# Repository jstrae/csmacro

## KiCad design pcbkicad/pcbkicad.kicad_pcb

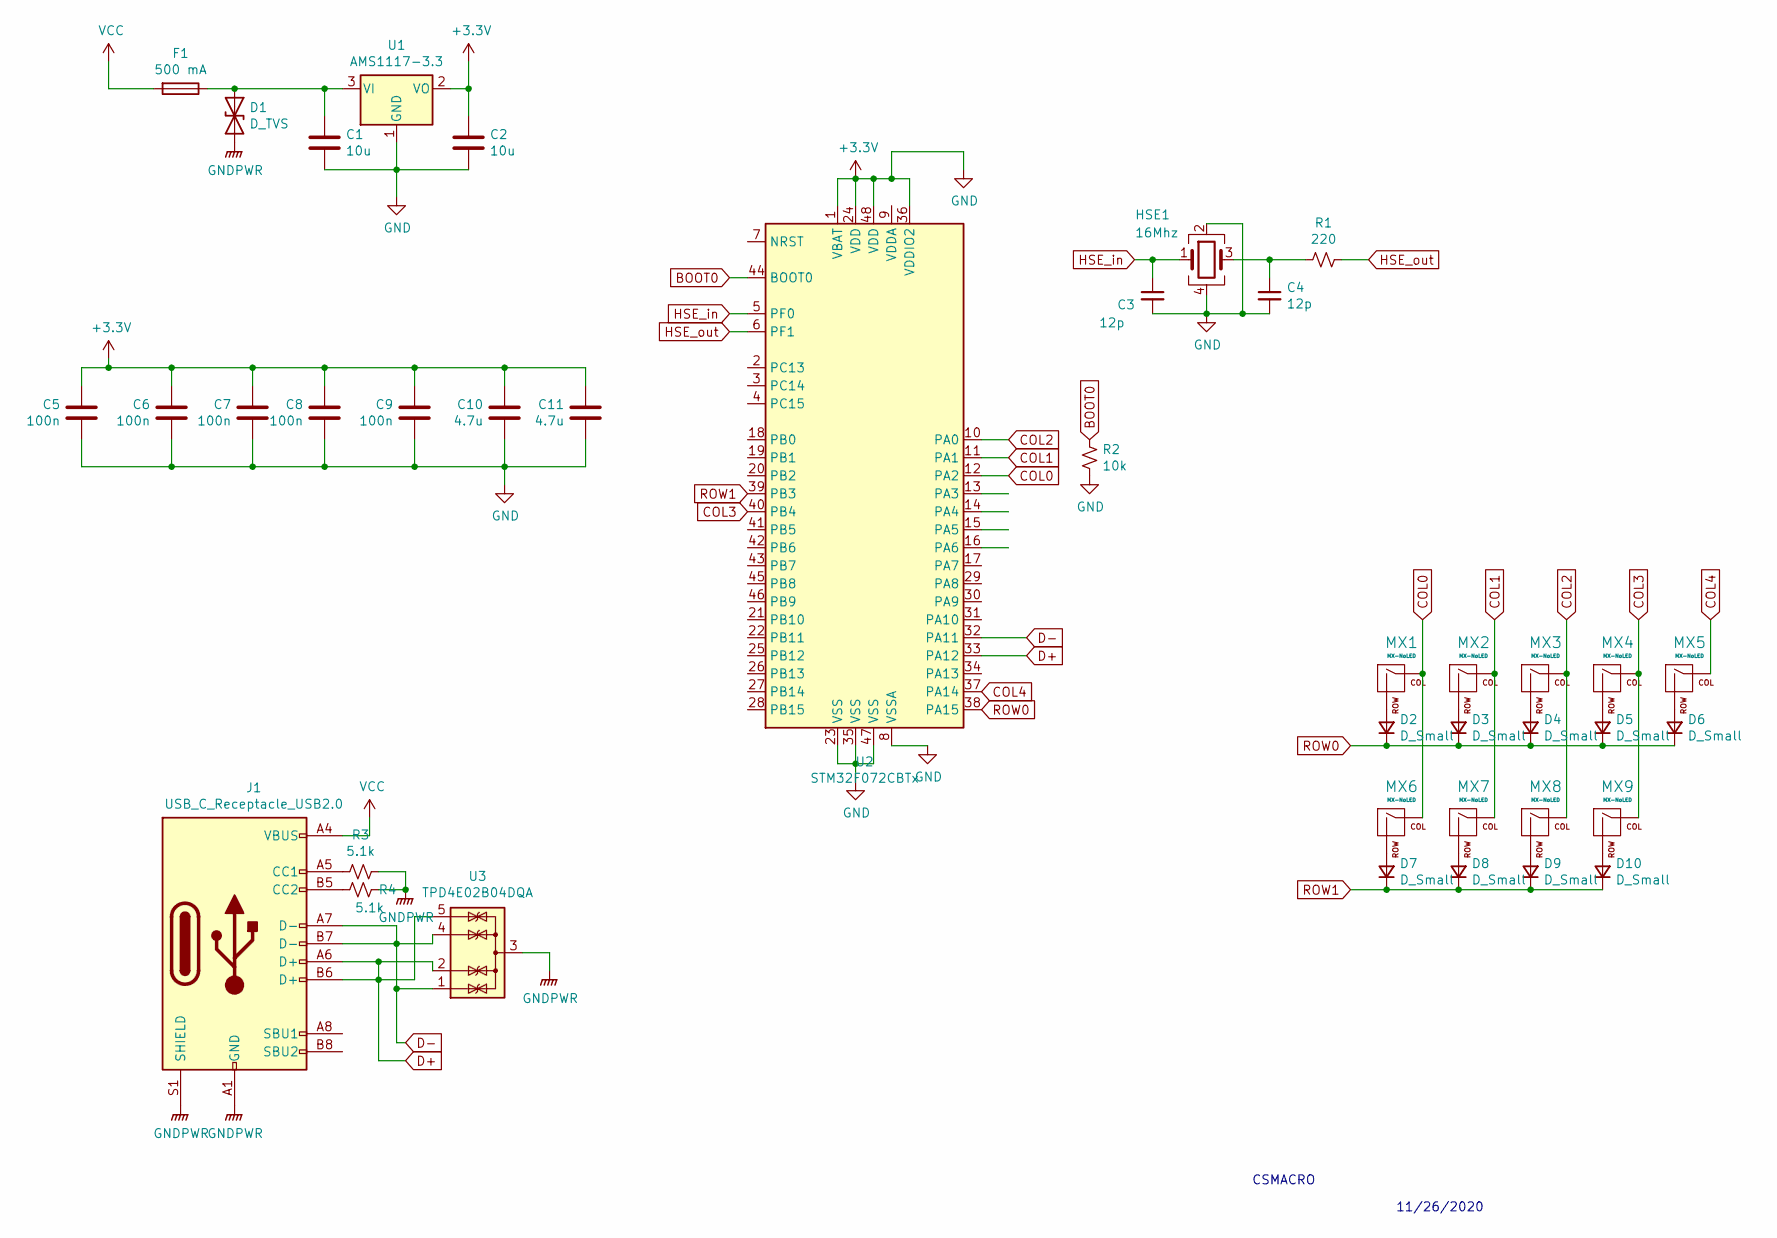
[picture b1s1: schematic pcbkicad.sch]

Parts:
C1: 10u; JST_SH_SM04B-SRSS-TB_1x04-1MP_P1.00mm_Horizontal
C2: 10u; C_0805_2012Metric
C3, C4: 12p; C_0805_2012Metric
C5, C6, C7, C8, C9: 100n; C_0805_2012Metric
C10, C11: 4.7u; C_0805_2012Metric
D1: D_TVS; D_0201_0603Metric
D2, D3, D4, D5, D6, D7, D8, D9, D10: D_Small; D_SOD-123
F1: 500 mA; Fuse_0402_1005Metric
HSE1: 16Mhz; Crystal_SMD_3225-4Pin_3.2x2.5mm
J1: USB_C_Receptacle_USB2.0; USB_C_Receptacle_HRO_TYPE-C-31-M-12
MX1, MX2, MX3, MX4, MX5, MX6, MX7, MX8, MX9: MX-NoLED; SW_Cherry_MX_1.00u_PCB
R1: 220; R_0805_2012Metric
R2: 10k; R_0805_2012Metric
R3, R4: 5.1k; R_0805_2012Metric
U1: AMS1117-3.3; SOT-223-3_TabPin2
U2: STM32F072CBTx; LQFP-48_7x7mm_P0.5mm
U3: TPD4E02B04DQA; USON-10_2.5x1.0mm_P0.5mm

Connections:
+3V3: C1.2, C2.1, C2.2, C3.2, C4.2, C5.1, C5.2, C6.1, C6.2, C7.1, C7.2, C8.1, C8.2, C9.1, C9.2, C10.1, C10.2, C11.1, C11.2, HSE1.2, HSE1.4, R2.2, U1.1 (GND), U1.2 (VO), U2.1 (VBAT), U2.8 (VSSA), U2.23 (VSS), U2.24 (VDD), U2.35 (VSS), U2.36 (VDDIO2), U2.47 (VSS), U2.48 (VDD)
BOOT0: R2.1, U2.44 (BOOT0)
COL0: MX1.1 (COL), MX6.1 (COL), U2.12 (PA2)
COL1: MX2.1 (COL), MX7.1 (COL), U2.11 (PA1)
COL2: MX3.1 (COL), MX8.1 (COL), U2.10 (PA0)
COL3: MX4.1 (COL), MX9.1 (COL), U2.40 (PB4)
COL4: MX5.1 (COL), U2.37 (PA14)
D+: J1.A6 (D+), J1.B6 (D+), U2.33 (PA12), U3.2 (IO2), U3.5 (IO4)
D-: J1.A7 (D-), J1.B7 (D-), U2.32 (PA11), U3.1 (IO1), U3.4 (IO3)
GNDPWR: D1.2 (A2), J1.A1 (GND), J1.A12 (GND), J1.B1 (GND), J1.B12 (GND), J1.S1 (SHIELD), R3.1, R4.1, U3.3 (G), U3.8 (G)
HSE_in: C3.1, HSE1.1, U2.5 (PF0)
HSE_out: R1.1, U2.6 (PF1)
unnamed: C1.1, D1.1 (A1), F1.1, U1.3 (VI)
unnamed: C4.1, HSE1.3, R1.2
unnamed: D2.2 (A), MX1.2 (ROW)
unnamed: D3.2 (A), MX2.2 (ROW)
unnamed: D4.2 (A), MX3.2 (ROW)
unnamed: D5.2 (A), MX4.2 (ROW)
unnamed: D6.2 (A), MX5.2 (ROW)
unnamed: D7.2 (A), MX6.2 (ROW)
unnamed: D8.2 (A), MX7.2 (ROW)
unnamed: D9.2 (A), MX8.2 (ROW)
unnamed: D10.2 (A), MX9.2 (ROW)
unnamed: J1.A5 (CC1), R3.2
unnamed: J1.B5 (CC2), R4.2
ROW0: D2.1 (K), D3.1 (K), D4.1 (K), D5.1 (K), D6.1 (K), U2.38 (PA15)
ROW1: D7.1 (K), D8.1 (K), D9.1 (K), D10.1 (K), U2.39 (PB3)
VCC: F1.2, J1.A4 (VBUS), J1.A9 (VBUS), J1.B4 (VBUS), J1.B9 (VBUS)

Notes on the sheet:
CSMACRO
11/26/2020

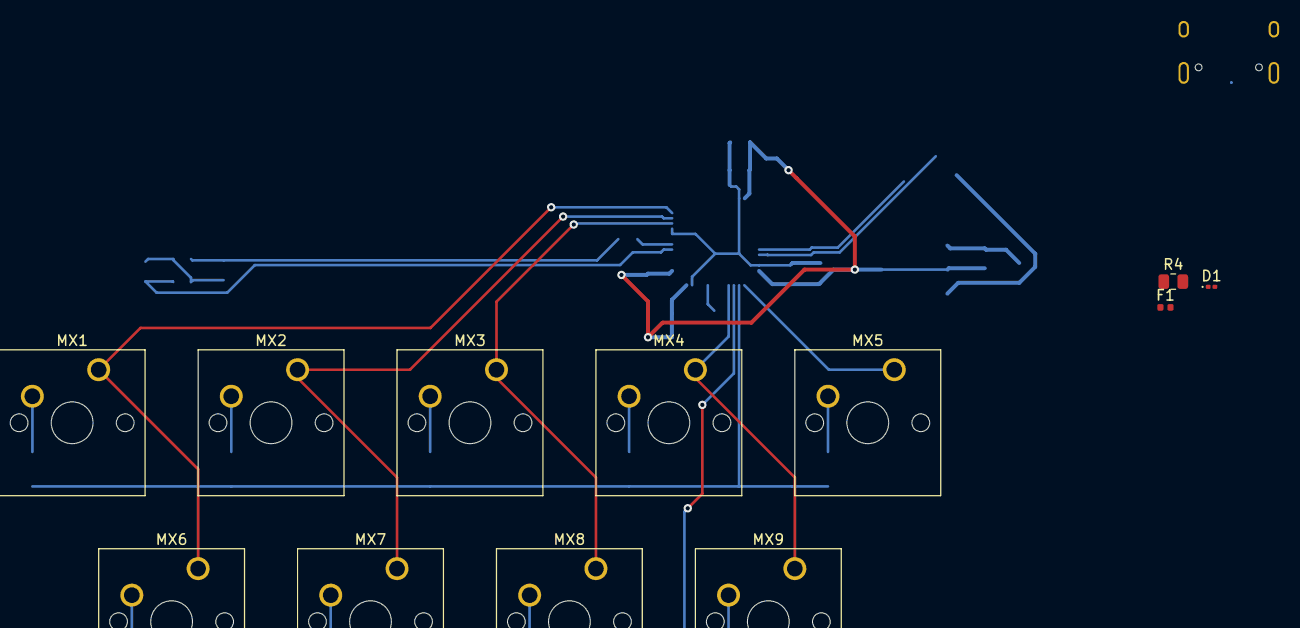
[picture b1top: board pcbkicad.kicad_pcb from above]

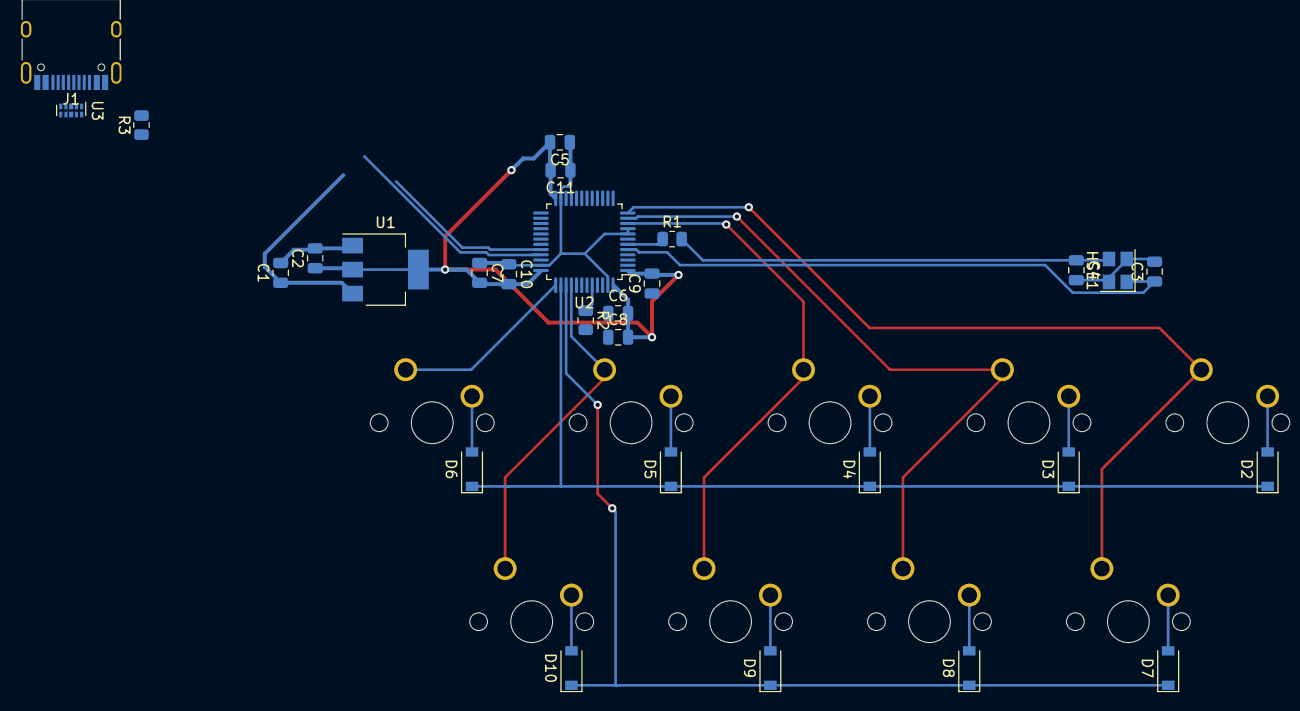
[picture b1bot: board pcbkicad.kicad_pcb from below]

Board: 2 copper layers, 40 parts (28 on the bottom side), 28 nets.

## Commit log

2020-11-26 Created KiCad project for PCB
2020-11-26 Added submodules
2020-11-26 Setup libraries
2020-11-26 Power managment and decoupling
2020-11-26 Replaced with a ChibiOS suppported mcu
2020-11-26 Added crystal
2020-11-26 Finsished rough draft of schematic
2020-11-26 Finished keyboard matrix
2020-11-26 Assigned footprints
2020-11-26 Finished most of pcb layout
2020-11-26 First attempt at routing
2020-11-26 Ground fill
2020-11-28 Started work with FreeCAD
2020-11-29 Rerouted and removed unecessary elements
2020-11-29 Schematic protection
2020-12-02 I honestly don't remember
